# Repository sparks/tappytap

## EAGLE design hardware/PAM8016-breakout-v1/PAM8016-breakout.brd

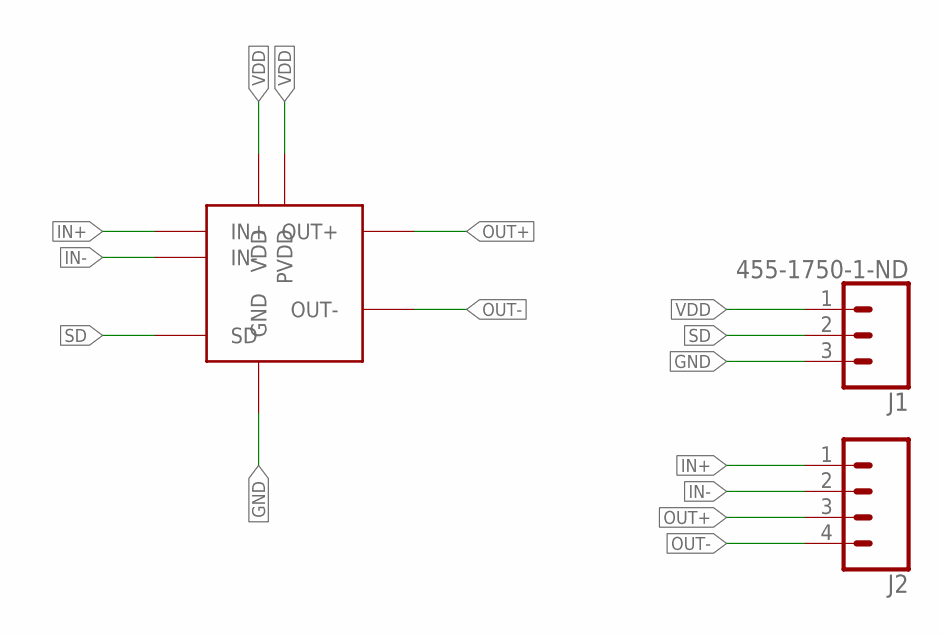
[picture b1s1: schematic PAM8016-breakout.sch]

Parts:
J1: 455-1750-1-ND; 1X03
J2: CONN_04; 1X04
U$1: PAM8016; U-FLGA1515-9

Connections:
GND: J1.3, U$1.A2 (GND), U$1.B3 (GND)
IN+: J2.1, U$1.A1 (IN+)
IN-: J2.2, U$1.C1 (IN-)
OUT+: J2.3, U$1.C3 (OUT+)
OUT-: J2.4, U$1.A3 (OUT-)
SD: J1.2, U$1.C2 (SD)
VDD: J1.1, U$1.B1 (VDD), U$1.B2 (PVDD)

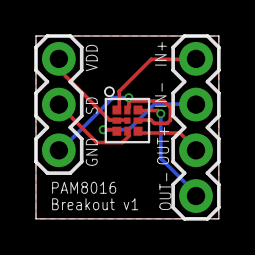
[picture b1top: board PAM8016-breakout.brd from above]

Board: 2 copper layers, 10.2 x 10.2 mm, 3 parts (0 on the bottom side), 7 nets.

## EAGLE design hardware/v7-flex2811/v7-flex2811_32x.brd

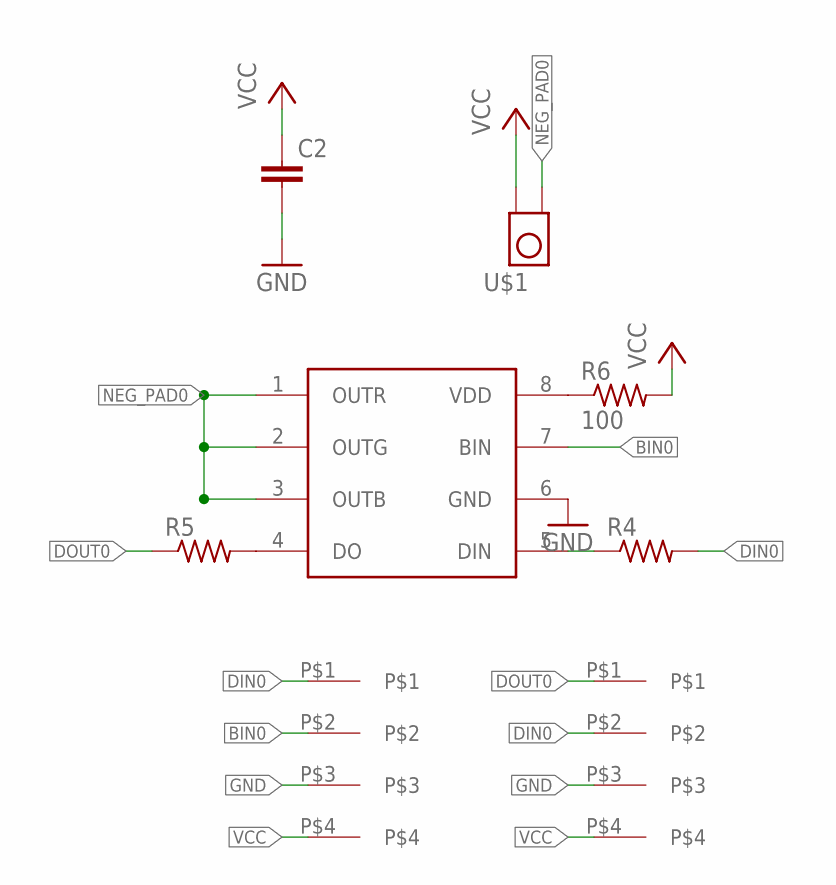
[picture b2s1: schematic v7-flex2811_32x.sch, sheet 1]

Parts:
C2: C-EUC0201; C0201
R4, R5: R-US_R0201; R0201
R6: 100; R0201
U1: WS2818; SO08
U$1: TP_4MM_MED_PAD
U$3, U$4: 4PAD

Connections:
BIN0: U1.7 (BIN), U$3.P$2
DIN0: R4.2, U$3.P$1, U$4.P$2; also elsewhere on the board
DOUT0: R5.1, U$4.P$1; also elsewhere on the board
GND: C2.2, U1.6 (GND), U$3.P$3, U$4.P$3; also elsewhere on the board
unnamed: R4.1, U1.5 (DIN)
unnamed: R5.2, U1.4 (DO)
unnamed: R6.1, U1.8 (VDD)
NEG_PAD0: U1.1 (OUTR), U1.2 (OUTG), U1.3 (OUTB), U$1.P$1 (0)
VCC: C2.1, R6.2, U$1.P$2 (1), U$3.P$4, U$4.P$4; also elsewhere on the board

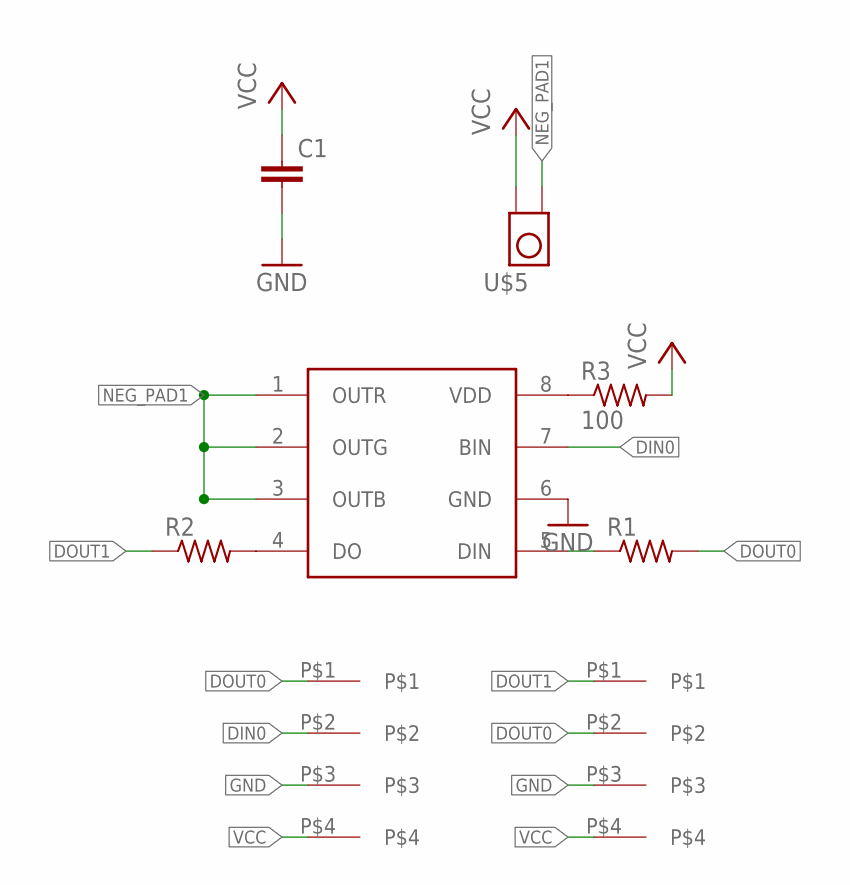
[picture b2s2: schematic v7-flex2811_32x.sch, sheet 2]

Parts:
C1: C-EUC0201; C0201
R1, R2: R-US_R0201; R0201
R3: 100; R0201
U2: WS2818; SO08
U$5: TP_4MM_MED_PAD
U$7, U$8: 4PAD

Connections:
DIN0: U2.7 (BIN), U$7.P$2; also elsewhere on the board
DOUT0: R1.2, U$7.P$1, U$8.P$2; also elsewhere on the board
DOUT1: R2.1, U$8.P$1; also elsewhere on the board
GND: C1.2, U2.6 (GND), U$7.P$3, U$8.P$3; also elsewhere on the board
unnamed: R1.1, U2.5 (DIN)
unnamed: R2.2, U2.4 (DO)
unnamed: R3.1, U2.8 (VDD)
NEG_PAD1: U2.1 (OUTR), U2.2 (OUTG), U2.3 (OUTB), U$5.P$1 (0)
VCC: C1.1, R3.2, U$5.P$2 (1), U$7.P$4, U$8.P$4; also elsewhere on the board

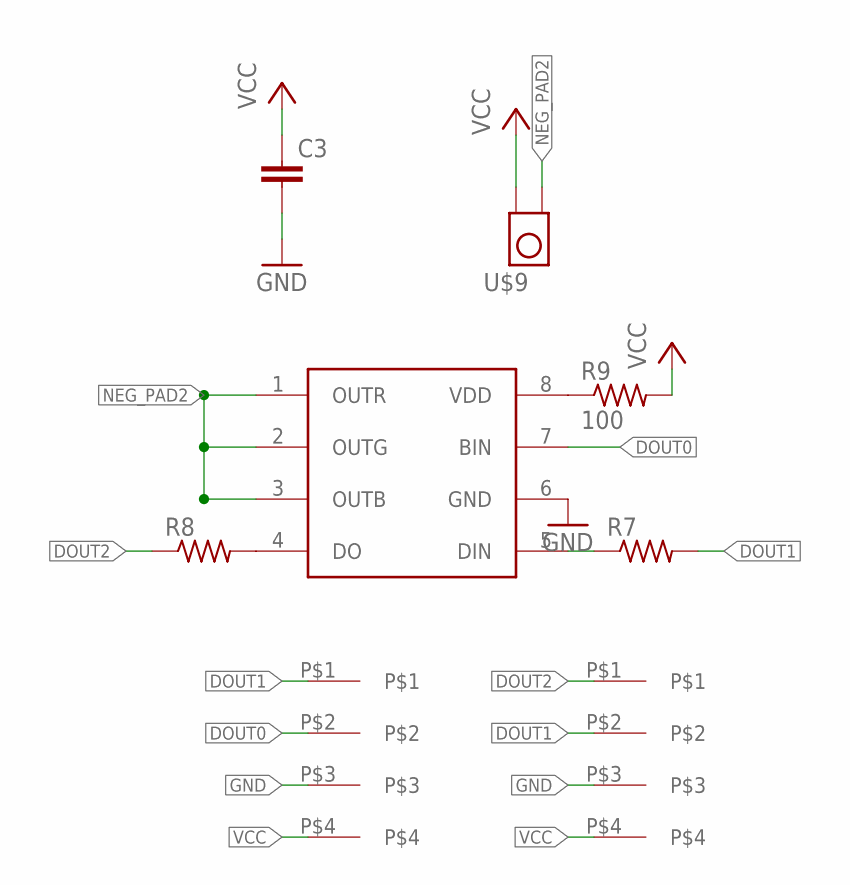
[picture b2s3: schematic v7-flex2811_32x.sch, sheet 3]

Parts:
C3: C-EUC0201; C0201
R7, R8: R-US_R0201; R0201
R9: 100; R0201
U3: WS2818; SO08
U$9: TP_4MM_MED_PAD
U$11, U$12: 4PAD

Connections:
DOUT0: U3.7 (BIN), U$11.P$2; also elsewhere on the board
DOUT1: R7.2, U$11.P$1, U$12.P$2; also elsewhere on the board
DOUT2: R8.1, U$12.P$1; also elsewhere on the board
GND: C3.2, U3.6 (GND), U$11.P$3, U$12.P$3; also elsewhere on the board
unnamed: R7.1, U3.5 (DIN)
unnamed: R8.2, U3.4 (DO)
unnamed: R9.1, U3.8 (VDD)
NEG_PAD2: U3.1 (OUTR), U3.2 (OUTG), U3.3 (OUTB), U$9.P$1 (0)
VCC: C3.1, R9.2, U$9.P$2 (1), U$11.P$4, U$12.P$4; also elsewhere on the board

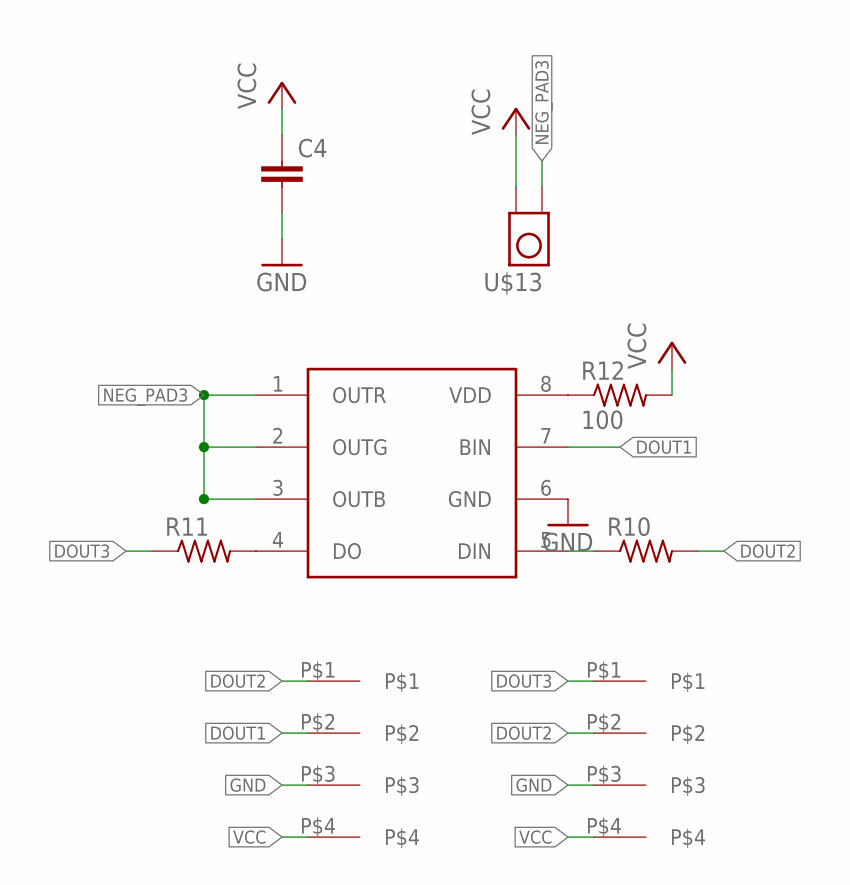
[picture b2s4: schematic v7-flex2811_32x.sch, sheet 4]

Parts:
C4: C-EUC0201; C0201
R10, R11: R-US_R0201; R0201
R12: 100; R0201
U4: WS2818; SO08
U$13: TP_4MM_MED_PAD
U$15, U$16: 4PAD

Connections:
DOUT1: U4.7 (BIN), U$15.P$2; also elsewhere on the board
DOUT2: R10.2, U$15.P$1, U$16.P$2; also elsewhere on the board
DOUT3: R11.1, U$16.P$1; also elsewhere on the board
GND: C4.2, U4.6 (GND), U$15.P$3, U$16.P$3; also elsewhere on the board
unnamed: R10.1, U4.5 (DIN)
unnamed: R11.2, U4.4 (DO)
unnamed: R12.1, U4.8 (VDD)
NEG_PAD3: U4.1 (OUTR), U4.2 (OUTG), U4.3 (OUTB), U$13.P$1 (0)
VCC: C4.1, R12.2, U$13.P$2 (1), U$15.P$4, U$16.P$4; also elsewhere on the board

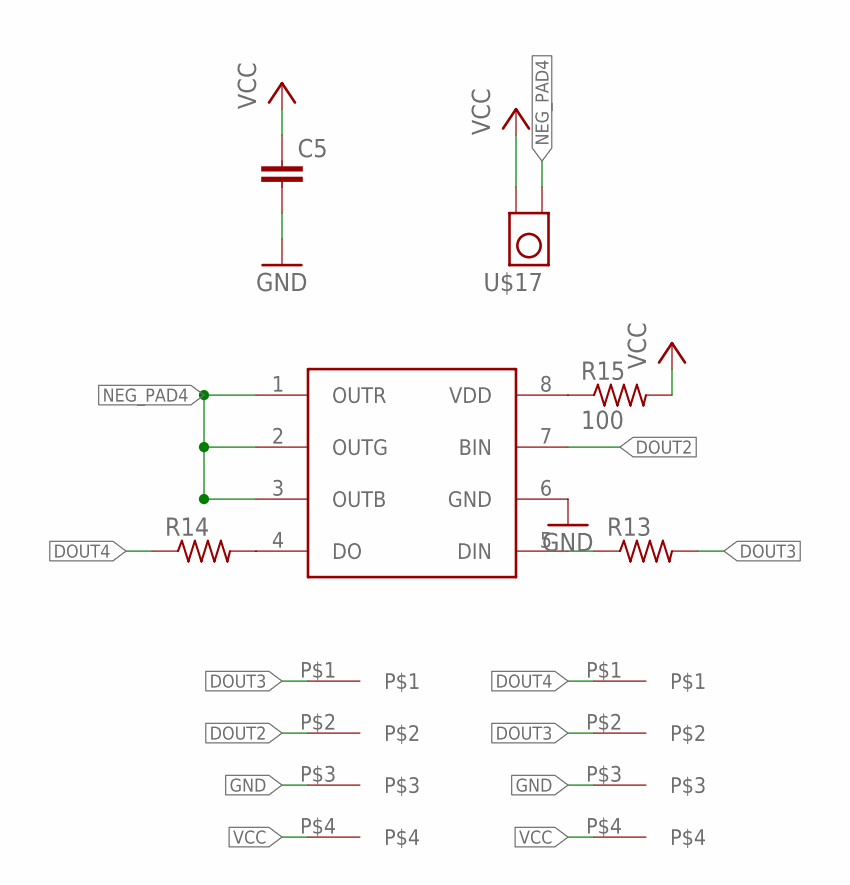
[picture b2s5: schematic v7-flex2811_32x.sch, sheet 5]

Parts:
C5: C-EUC0201; C0201
R13, R14: R-US_R0201; R0201
R15: 100; R0201
U5: WS2818; SO08
U$17: TP_4MM_MED_PAD
U$19, U$20: 4PAD

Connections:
DOUT2: U5.7 (BIN), U$19.P$2; also elsewhere on the board
DOUT3: R13.2, U$19.P$1, U$20.P$2; also elsewhere on the board
DOUT4: R14.1, U$20.P$1; also elsewhere on the board
GND: C5.2, U5.6 (GND), U$19.P$3, U$20.P$3; also elsewhere on the board
unnamed: R13.1, U5.5 (DIN)
unnamed: R14.2, U5.4 (DO)
unnamed: R15.1, U5.8 (VDD)
NEG_PAD4: U5.1 (OUTR), U5.2 (OUTG), U5.3 (OUTB), U$17.P$1 (0)
VCC: C5.1, R15.2, U$17.P$2 (1), U$19.P$4, U$20.P$4; also elsewhere on the board

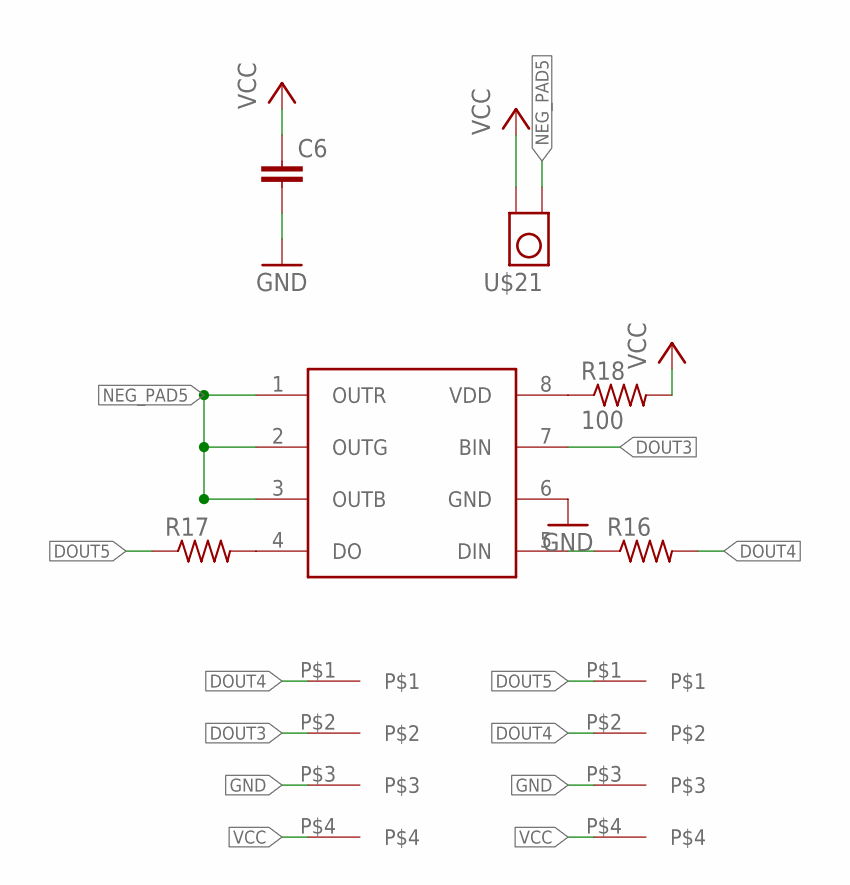
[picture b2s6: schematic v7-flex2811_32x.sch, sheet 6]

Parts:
C6: C-EUC0201; C0201
R16, R17: R-US_R0201; R0201
R18: 100; R0201
U6: WS2818; SO08
U$21: TP_4MM_MED_PAD
U$23, U$24: 4PAD

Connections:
DOUT3: U6.7 (BIN), U$23.P$2; also elsewhere on the board
DOUT4: R16.2, U$23.P$1, U$24.P$2; also elsewhere on the board
DOUT5: R17.1, U$24.P$1; also elsewhere on the board
GND: C6.2, U6.6 (GND), U$23.P$3, U$24.P$3; also elsewhere on the board
unnamed: R16.1, U6.5 (DIN)
unnamed: R17.2, U6.4 (DO)
unnamed: R18.1, U6.8 (VDD)
NEG_PAD5: U6.1 (OUTR), U6.2 (OUTG), U6.3 (OUTB), U$21.P$1 (0)
VCC: C6.1, R18.2, U$21.P$2 (1), U$23.P$4, U$24.P$4; also elsewhere on the board

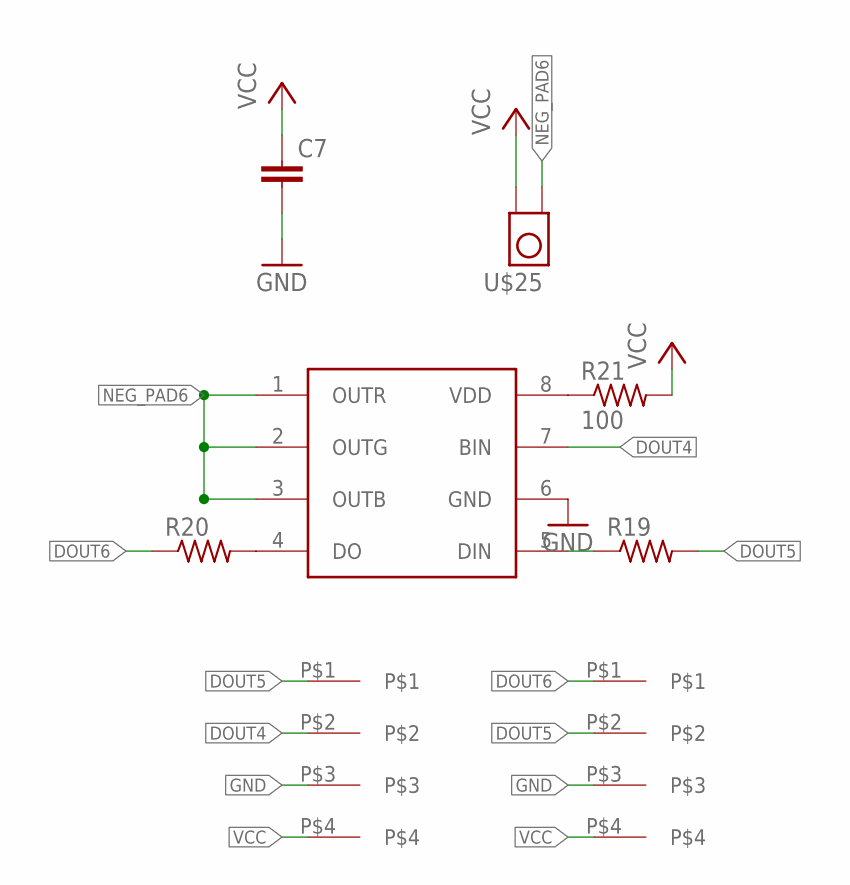
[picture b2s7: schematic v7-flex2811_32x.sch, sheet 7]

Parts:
C7: C-EUC0201; C0201
R19, R20: R-US_R0201; R0201
R21: 100; R0201
U7: WS2818; SO08
U$25: TP_4MM_MED_PAD
U$27, U$28: 4PAD

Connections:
DOUT4: U7.7 (BIN), U$27.P$2; also elsewhere on the board
DOUT5: R19.2, U$27.P$1, U$28.P$2; also elsewhere on the board
DOUT6: R20.1, U$28.P$1; also elsewhere on the board
GND: C7.2, U7.6 (GND), U$27.P$3, U$28.P$3; also elsewhere on the board
unnamed: R19.1, U7.5 (DIN)
unnamed: R20.2, U7.4 (DO)
unnamed: R21.1, U7.8 (VDD)
NEG_PAD6: U7.1 (OUTR), U7.2 (OUTG), U7.3 (OUTB), U$25.P$1 (0)
VCC: C7.1, R21.2, U$25.P$2 (1), U$27.P$4, U$28.P$4; also elsewhere on the board

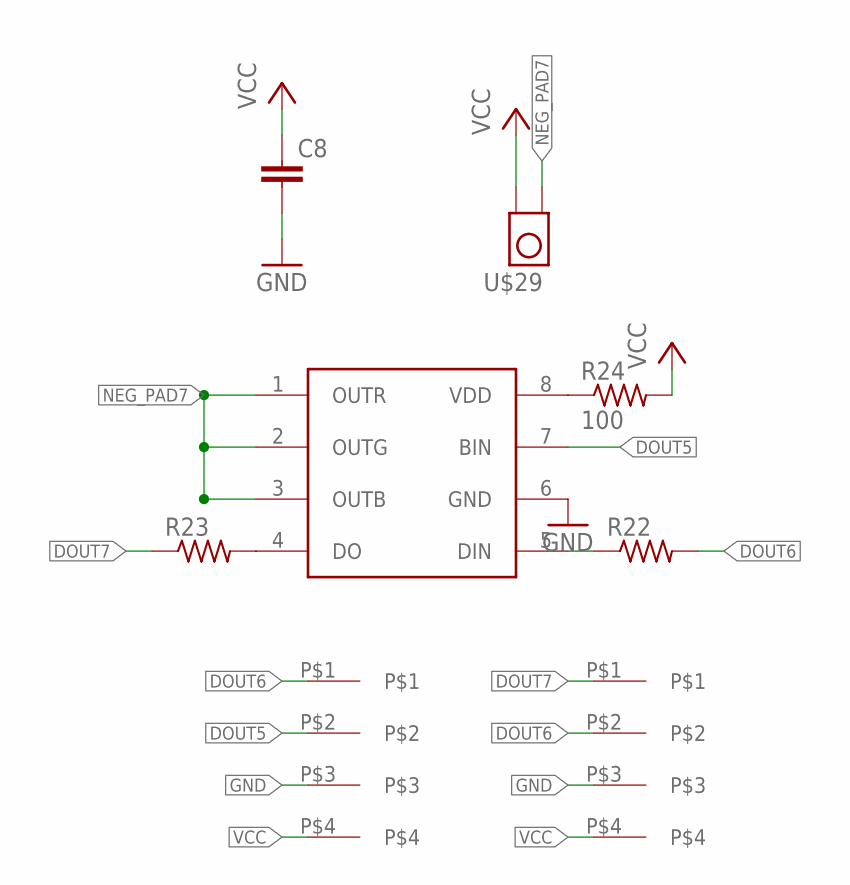
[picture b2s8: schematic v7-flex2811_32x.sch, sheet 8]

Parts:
C8: C-EUC0201; C0201
R22, R23: R-US_R0201; R0201
R24: 100; R0201
U8: WS2818; SO08
U$29: TP_4MM_MED_PAD
U$31, U$32: 4PAD

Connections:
DOUT5: U8.7 (BIN), U$31.P$2; also elsewhere on the board
DOUT6: R22.2, U$31.P$1, U$32.P$2; also elsewhere on the board
DOUT7: R23.1, U$32.P$1; also elsewhere on the board
GND: C8.2, U8.6 (GND), U$31.P$3, U$32.P$3; also elsewhere on the board
unnamed: R22.1, U8.5 (DIN)
unnamed: R23.2, U8.4 (DO)
unnamed: R24.1, U8.8 (VDD)
NEG_PAD7: U8.1 (OUTR), U8.2 (OUTG), U8.3 (OUTB), U$29.P$1 (0)
VCC: C8.1, R24.2, U$29.P$2 (1), U$31.P$4, U$32.P$4; also elsewhere on the board

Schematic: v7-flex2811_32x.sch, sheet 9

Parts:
C9: C-EUC0201; C0201
R25, R26: R-US_R0201; R0201
R27: 100; R0201
U9: WS2818; SO08
U$33: TP_4MM_MED_PAD
U$35, U$36: 4PAD

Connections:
DOUT6: U9.7 (BIN), U$35.P$2; also elsewhere on the board
DOUT7: R25.2, U$35.P$1, U$36.P$2; also elsewhere on the board
DOUT8: R26.1, U$36.P$1; also elsewhere on the board
GND: C9.2, U9.6 (GND), U$35.P$3, U$36.P$3; also elsewhere on the board
unnamed: R25.1, U9.5 (DIN)
unnamed: R26.2, U9.4 (DO)
unnamed: R27.1, U9.8 (VDD)
NEG_PAD8: U9.1 (OUTR), U9.2 (OUTG), U9.3 (OUTB), U$33.P$1 (0)
VCC: C9.1, R27.2, U$33.P$2 (1), U$35.P$4, U$36.P$4; also elsewhere on the board

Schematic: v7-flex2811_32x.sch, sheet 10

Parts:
C10: C-EUC0201; C0201
R28, R29: R-US_R0201; R0201
R30: 100; R0201
U10: WS2818; SO08
U$37: TP_4MM_MED_PAD
U$39, U$40: 4PAD

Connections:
DOUT7: U10.7 (BIN), U$39.P$2; also elsewhere on the board
DOUT8: R28.2, U$39.P$1, U$40.P$2; also elsewhere on the board
DOUT9: R29.1, U$40.P$1; also elsewhere on the board
GND: C10.2, U10.6 (GND), U$39.P$3, U$40.P$3; also elsewhere on the board
unnamed: R28.1, U10.5 (DIN)
unnamed: R29.2, U10.4 (DO)
unnamed: R30.1, U10.8 (VDD)
NEG_PAD9: U10.1 (OUTR), U10.2 (OUTG), U10.3 (OUTB), U$37.P$1 (0)
VCC: C10.1, R30.2, U$37.P$2 (1), U$39.P$4, U$40.P$4; also elsewhere on the board

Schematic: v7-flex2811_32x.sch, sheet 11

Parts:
C11: C-EUC0201; C0201
R31, R32: R-US_R0201; R0201
R33: 100; R0201
U11: WS2818; SO08
U$41: TP_4MM_MED_PAD
U$43, U$44: 4PAD

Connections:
DOUT8: U11.7 (BIN), U$43.P$2; also elsewhere on the board
DOUT9: R31.2, U$43.P$1, U$44.P$2; also elsewhere on the board
DOUT10: R32.1, U$44.P$1; also elsewhere on the board
GND: C11.2, U11.6 (GND), U$43.P$3, U$44.P$3; also elsewhere on the board
unnamed: R31.1, U11.5 (DIN)
unnamed: R32.2, U11.4 (DO)
unnamed: R33.1, U11.8 (VDD)
NEG_PAD10: U11.1 (OUTR), U11.2 (OUTG), U11.3 (OUTB), U$41.P$1 (0)
VCC: C11.1, R33.2, U$41.P$2 (1), U$43.P$4, U$44.P$4; also elsewhere on the board

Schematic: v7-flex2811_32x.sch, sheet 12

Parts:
C12: C-EUC0201; C0201
R34, R35: R-US_R0201; R0201
R36: 100; R0201
U12: WS2818; SO08
U$45: TP_4MM_MED_PAD
U$47, U$48: 4PAD

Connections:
DOUT9: U12.7 (BIN), U$47.P$2; also elsewhere on the board
DOUT10: R34.2, U$47.P$1, U$48.P$2; also elsewhere on the board
DOUT11: R35.1, U$48.P$1; also elsewhere on the board
GND: C12.2, U12.6 (GND), U$47.P$3, U$48.P$3; also elsewhere on the board
unnamed: R34.1, U12.5 (DIN)
unnamed: R35.2, U12.4 (DO)
unnamed: R36.1, U12.8 (VDD)
NEG_PAD11: U12.1 (OUTR), U12.2 (OUTG), U12.3 (OUTB), U$45.P$1 (0)
VCC: C12.1, R36.2, U$45.P$2 (1), U$47.P$4, U$48.P$4; also elsewhere on the board

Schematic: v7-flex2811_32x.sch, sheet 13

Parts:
C13: C-EUC0201; C0201
R37, R38: R-US_R0201; R0201
R39: 100; R0201
U13: WS2818; SO08
U$49: TP_4MM_MED_PAD
U$51, U$52: 4PAD

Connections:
DOUT10: U13.7 (BIN), U$51.P$2; also elsewhere on the board
DOUT11: R37.2, U$51.P$1, U$52.P$2; also elsewhere on the board
DOUT12: R38.1, U$52.P$1; also elsewhere on the board
GND: C13.2, U13.6 (GND), U$51.P$3, U$52.P$3; also elsewhere on the board
unnamed: R37.1, U13.5 (DIN)
unnamed: R38.2, U13.4 (DO)
unnamed: R39.1, U13.8 (VDD)
NEG_PAD12: U13.1 (OUTR), U13.2 (OUTG), U13.3 (OUTB), U$49.P$1 (0)
VCC: C13.1, R39.2, U$49.P$2 (1), U$51.P$4, U$52.P$4; also elsewhere on the board

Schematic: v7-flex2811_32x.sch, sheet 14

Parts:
C14: C-EUC0201; C0201
R40, R41: R-US_R0201; R0201
R42: 100; R0201
U14: WS2818; SO08
U$53: TP_4MM_MED_PAD
U$55, U$56: 4PAD

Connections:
DOUT11: U14.7 (BIN), U$55.P$2; also elsewhere on the board
DOUT12: R40.2, U$55.P$1, U$56.P$2; also elsewhere on the board
DOUT13: R41.1, U$56.P$1; also elsewhere on the board
GND: C14.2, U14.6 (GND), U$55.P$3, U$56.P$3; also elsewhere on the board
unnamed: R40.1, U14.5 (DIN)
unnamed: R41.2, U14.4 (DO)
unnamed: R42.1, U14.8 (VDD)
NEG_PAD13: U14.1 (OUTR), U14.2 (OUTG), U14.3 (OUTB), U$53.P$1 (0)
VCC: C14.1, R42.2, U$53.P$2 (1), U$55.P$4, U$56.P$4; also elsewhere on the board

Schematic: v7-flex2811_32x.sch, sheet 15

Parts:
C15: C-EUC0201; C0201
R43, R44: R-US_R0201; R0201
R45: 100; R0201
U15: WS2818; SO08
U$57: TP_4MM_MED_PAD
U$59, U$60: 4PAD

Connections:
DOUT12: U15.7 (BIN), U$59.P$2; also elsewhere on the board
DOUT13: R43.2, U$59.P$1, U$60.P$2; also elsewhere on the board
DOUT14: R44.1, U$60.P$1; also elsewhere on the board
GND: C15.2, U15.6 (GND), U$59.P$3, U$60.P$3; also elsewhere on the board
unnamed: R43.1, U15.5 (DIN)
unnamed: R44.2, U15.4 (DO)
unnamed: R45.1, U15.8 (VDD)
NEG_PAD14: U15.1 (OUTR), U15.2 (OUTG), U15.3 (OUTB), U$57.P$1 (0)
VCC: C15.1, R45.2, U$57.P$2 (1), U$59.P$4, U$60.P$4; also elsewhere on the board

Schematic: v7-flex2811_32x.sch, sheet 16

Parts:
C16: C-EUC0201; C0201
R46, R47: R-US_R0201; R0201
R48: 100; R0201
U16: WS2818; SO08
U$61: TP_4MM_MED_PAD
U$63, U$64: 4PAD

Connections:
DOUT13: U16.7 (BIN), U$63.P$2; also elsewhere on the board
DOUT14: R46.2, U$63.P$1, U$64.P$2; also elsewhere on the board
DOUT15: R47.1, U$64.P$1; also elsewhere on the board
GND: C16.2, U16.6 (GND), U$63.P$3, U$64.P$3; also elsewhere on the board
unnamed: R46.1, U16.5 (DIN)
unnamed: R47.2, U16.4 (DO)
unnamed: R48.1, U16.8 (VDD)
NEG_PAD15: U16.1 (OUTR), U16.2 (OUTG), U16.3 (OUTB), U$61.P$1 (0)
VCC: C16.1, R48.2, U$61.P$2 (1), U$63.P$4, U$64.P$4; also elsewhere on the board

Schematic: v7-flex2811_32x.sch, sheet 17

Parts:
C17: C-EUC0201; C0201
R49, R50: R-US_R0201; R0201
R51: 100; R0201
U17: WS2818; SO08
U$65: TP_4MM_MED_PAD
U$67, U$68: 4PAD

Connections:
DOUT14: U17.7 (BIN), U$67.P$2; also elsewhere on the board
DOUT15: R49.2, U$67.P$1, U$68.P$2; also elsewhere on the board
DOUT16: R50.1, U$68.P$1; also elsewhere on the board
GND: C17.2, U17.6 (GND), U$67.P$3, U$68.P$3; also elsewhere on the board
unnamed: R49.1, U17.5 (DIN)
unnamed: R50.2, U17.4 (DO)
unnamed: R51.1, U17.8 (VDD)
NEG_PAD16: U17.1 (OUTR), U17.2 (OUTG), U17.3 (OUTB), U$65.P$1 (0)
VCC: C17.1, R51.2, U$65.P$2 (1), U$67.P$4, U$68.P$4; also elsewhere on the board

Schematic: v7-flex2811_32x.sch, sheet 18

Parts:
C18: C-EUC0201; C0201
R52, R53: R-US_R0201; R0201
R54: 100; R0201
U18: WS2818; SO08
U$69: TP_4MM_MED_PAD
U$71, U$72: 4PAD

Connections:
DOUT15: U18.7 (BIN), U$71.P$2; also elsewhere on the board
DOUT16: R52.2, U$71.P$1, U$72.P$2; also elsewhere on the board
DOUT17: R53.1, U$72.P$1; also elsewhere on the board
GND: C18.2, U18.6 (GND), U$71.P$3, U$72.P$3; also elsewhere on the board
unnamed: R52.1, U18.5 (DIN)
unnamed: R53.2, U18.4 (DO)
unnamed: R54.1, U18.8 (VDD)
NEG_PAD17: U18.1 (OUTR), U18.2 (OUTG), U18.3 (OUTB), U$69.P$1 (0)
VCC: C18.1, R54.2, U$69.P$2 (1), U$71.P$4, U$72.P$4; also elsewhere on the board

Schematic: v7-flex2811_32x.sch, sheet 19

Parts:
C19: C-EUC0201; C0201
R55, R56: R-US_R0201; R0201
R57: 100; R0201
U19: WS2818; SO08
U$73: TP_4MM_MED_PAD
U$75, U$76: 4PAD

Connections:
DOUT16: U19.7 (BIN), U$75.P$2; also elsewhere on the board
DOUT17: R55.2, U$75.P$1, U$76.P$2; also elsewhere on the board
DOUT18: R56.1, U$76.P$1; also elsewhere on the board
GND: C19.2, U19.6 (GND), U$75.P$3, U$76.P$3; also elsewhere on the board
unnamed: R55.1, U19.5 (DIN)
unnamed: R56.2, U19.4 (DO)
unnamed: R57.1, U19.8 (VDD)
NEG_PAD18: U19.1 (OUTR), U19.2 (OUTG), U19.3 (OUTB), U$73.P$1 (0)
VCC: C19.1, R57.2, U$73.P$2 (1), U$75.P$4, U$76.P$4; also elsewhere on the board

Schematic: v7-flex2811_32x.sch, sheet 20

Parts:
C20: C-EUC0201; C0201
R58, R59: R-US_R0201; R0201
R60: 100; R0201
U20: WS2818; SO08
U$77: TP_4MM_MED_PAD
U$79, U$80: 4PAD

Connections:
DOUT17: U20.7 (BIN), U$79.P$2; also elsewhere on the board
DOUT18: R58.2, U$79.P$1, U$80.P$2; also elsewhere on the board
DOUT19: R59.1, U$80.P$1; also elsewhere on the board
GND: C20.2, U20.6 (GND), U$79.P$3, U$80.P$3; also elsewhere on the board
unnamed: R58.1, U20.5 (DIN)
unnamed: R59.2, U20.4 (DO)
unnamed: R60.1, U20.8 (VDD)
NEG_PAD19: U20.1 (OUTR), U20.2 (OUTG), U20.3 (OUTB), U$77.P$1 (0)
VCC: C20.1, R60.2, U$77.P$2 (1), U$79.P$4, U$80.P$4; also elsewhere on the board

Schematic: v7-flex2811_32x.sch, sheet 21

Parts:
C21: C-EUC0201; C0201
R61, R62: R-US_R0201; R0201
R63: 100; R0201
U21: WS2818; SO08
U$81: TP_4MM_MED_PAD
U$83, U$84: 4PAD

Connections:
DOUT18: U21.7 (BIN), U$83.P$2; also elsewhere on the board
DOUT19: R61.2, U$83.P$1, U$84.P$2; also elsewhere on the board
DOUT20: R62.1, U$84.P$1; also elsewhere on the board
GND: C21.2, U21.6 (GND), U$83.P$3, U$84.P$3; also elsewhere on the board
unnamed: R61.1, U21.5 (DIN)
unnamed: R62.2, U21.4 (DO)
unnamed: R63.1, U21.8 (VDD)
NEG_PAD20: U21.1 (OUTR), U21.2 (OUTG), U21.3 (OUTB), U$81.P$1 (0)
VCC: C21.1, R63.2, U$81.P$2 (1), U$83.P$4, U$84.P$4; also elsewhere on the board

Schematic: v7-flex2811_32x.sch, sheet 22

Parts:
C22: C-EUC0201; C0201
R64, R65: R-US_R0201; R0201
R66: 100; R0201
U22: WS2818; SO08
U$85: TP_4MM_MED_PAD
U$87, U$88: 4PAD

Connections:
DOUT19: U22.7 (BIN), U$87.P$2; also elsewhere on the board
DOUT20: R64.2, U$87.P$1, U$88.P$2; also elsewhere on the board
DOUT21: R65.1, U$88.P$1; also elsewhere on the board
GND: C22.2, U22.6 (GND), U$87.P$3, U$88.P$3; also elsewhere on the board
unnamed: R64.1, U22.5 (DIN)
unnamed: R65.2, U22.4 (DO)
unnamed: R66.1, U22.8 (VDD)
NEG_PAD21: U22.1 (OUTR), U22.2 (OUTG), U22.3 (OUTB), U$85.P$1 (0)
VCC: C22.1, R66.2, U$85.P$2 (1), U$87.P$4, U$88.P$4; also elsewhere on the board

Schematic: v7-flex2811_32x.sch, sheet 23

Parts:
C23: C-EUC0201; C0201
R67, R68: R-US_R0201; R0201
R69: 100; R0201
U23: WS2818; SO08
U$89: TP_4MM_MED_PAD
U$91, U$92: 4PAD

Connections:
DOUT20: U23.7 (BIN), U$91.P$2; also elsewhere on the board
DOUT21: R67.2, U$91.P$1, U$92.P$2; also elsewhere on the board
DOUT22: R68.1, U$92.P$1; also elsewhere on the board
GND: C23.2, U23.6 (GND), U$91.P$3, U$92.P$3; also elsewhere on the board
unnamed: R67.1, U23.5 (DIN)
unnamed: R68.2, U23.4 (DO)
unnamed: R69.1, U23.8 (VDD)
NEG_PAD22: U23.1 (OUTR), U23.2 (OUTG), U23.3 (OUTB), U$89.P$1 (0)
VCC: C23.1, R69.2, U$89.P$2 (1), U$91.P$4, U$92.P$4; also elsewhere on the board

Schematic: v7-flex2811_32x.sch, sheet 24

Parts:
C24: C-EUC0201; C0201
R70, R71: R-US_R0201; R0201
R72: 100; R0201
U24: WS2818; SO08
U$93: TP_4MM_MED_PAD
U$95, U$96: 4PAD

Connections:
DOUT21: U24.7 (BIN), U$95.P$2; also elsewhere on the board
DOUT22: R70.2, U$95.P$1, U$96.P$2; also elsewhere on the board
DOUT23: R71.1, U$96.P$1; also elsewhere on the board
GND: C24.2, U24.6 (GND), U$95.P$3, U$96.P$3; also elsewhere on the board
unnamed: R70.1, U24.5 (DIN)
unnamed: R71.2, U24.4 (DO)
unnamed: R72.1, U24.8 (VDD)
NEG_PAD23: U24.1 (OUTR), U24.2 (OUTG), U24.3 (OUTB), U$93.P$1 (0)
VCC: C24.1, R72.2, U$93.P$2 (1), U$95.P$4, U$96.P$4; also elsewhere on the board

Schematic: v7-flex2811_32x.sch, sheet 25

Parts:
C25: C-EUC0201; C0201
R73, R74: R-US_R0201; R0201
R75: 100; R0201
U25: WS2818; SO08
U$97: TP_4MM_MED_PAD
U$99, U$100: 4PAD

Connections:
DOUT22: U25.7 (BIN), U$99.P$2; also elsewhere on the board
DOUT23: R73.2, U$99.P$1, U$100.P$2; also elsewhere on the board
DOUT24: R74.1, U$100.P$1; also elsewhere on the board
GND: C25.2, U25.6 (GND), U$99.P$3, U$100.P$3; also elsewhere on the board
unnamed: R73.1, U25.5 (DIN)
unnamed: R74.2, U25.4 (DO)
unnamed: R75.1, U25.8 (VDD)
NEG_PAD24: U25.1 (OUTR), U25.2 (OUTG), U25.3 (OUTB), U$97.P$1 (0)
VCC: C25.1, R75.2, U$97.P$2 (1), U$99.P$4, U$100.P$4; also elsewhere on the board

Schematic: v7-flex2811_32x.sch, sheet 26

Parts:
C26: C-EUC0201; C0201
R76, R77: R-US_R0201; R0201
R78: 100; R0201
U26: WS2818; SO08
U$101: TP_4MM_MED_PAD
U$103, U$104: 4PAD

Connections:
DOUT23: U26.7 (BIN), U$103.P$2; also elsewhere on the board
DOUT24: R76.2, U$103.P$1, U$104.P$2; also elsewhere on the board
DOUT25: R77.1, U$104.P$1; also elsewhere on the board
GND: C26.2, U26.6 (GND), U$103.P$3, U$104.P$3; also elsewhere on the board
unnamed: R76.1, U26.5 (DIN)
unnamed: R77.2, U26.4 (DO)
unnamed: R78.1, U26.8 (VDD)
NEG_PAD25: U26.1 (OUTR), U26.2 (OUTG), U26.3 (OUTB), U$101.P$1 (0)
VCC: C26.1, R78.2, U$101.P$2 (1), U$103.P$4, U$104.P$4; also elsewhere on the board

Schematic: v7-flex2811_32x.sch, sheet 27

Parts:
C27: C-EUC0201; C0201
R79, R80: R-US_R0201; R0201
R81: 100; R0201
U27: WS2818; SO08
U$105: TP_4MM_MED_PAD
U$107, U$108: 4PAD

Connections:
DOUT24: U27.7 (BIN), U$107.P$2; also elsewhere on the board
DOUT25: R79.2, U$107.P$1, U$108.P$2; also elsewhere on the board
DOUT26: R80.1, U$108.P$1; also elsewhere on the board
GND: C27.2, U27.6 (GND), U$107.P$3, U$108.P$3; also elsewhere on the board
unnamed: R79.1, U27.5 (DIN)
unnamed: R80.2, U27.4 (DO)
unnamed: R81.1, U27.8 (VDD)
NEG_PAD26: U27.1 (OUTR), U27.2 (OUTG), U27.3 (OUTB), U$105.P$1 (0)
VCC: C27.1, R81.2, U$105.P$2 (1), U$107.P$4, U$108.P$4; also elsewhere on the board

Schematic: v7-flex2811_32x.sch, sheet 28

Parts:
C28: C-EUC0201; C0201
R82, R83: R-US_R0201; R0201
R84: 100; R0201
U28: WS2818; SO08
U$109: TP_4MM_MED_PAD
U$111, U$112: 4PAD

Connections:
DOUT25: U28.7 (BIN), U$111.P$2; also elsewhere on the board
DOUT26: R82.2, U$111.P$1, U$112.P$2; also elsewhere on the board
DOUT27: R83.1, U$112.P$1; also elsewhere on the board
GND: C28.2, U28.6 (GND), U$111.P$3, U$112.P$3; also elsewhere on the board
unnamed: R82.1, U28.5 (DIN)
unnamed: R83.2, U28.4 (DO)
unnamed: R84.1, U28.8 (VDD)
NEG_PAD27: U28.1 (OUTR), U28.2 (OUTG), U28.3 (OUTB), U$109.P$1 (0)
VCC: C28.1, R84.2, U$109.P$2 (1), U$111.P$4, U$112.P$4; also elsewhere on the board

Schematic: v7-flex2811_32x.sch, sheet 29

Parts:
C29: C-EUC0201; C0201
R85, R86: R-US_R0201; R0201
R87: 100; R0201
U29: WS2818; SO08
U$113: TP_4MM_MED_PAD
U$115, U$116: 4PAD

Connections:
DOUT26: U29.7 (BIN), U$115.P$2; also elsewhere on the board
DOUT27: R85.2, U$115.P$1, U$116.P$2; also elsewhere on the board
DOUT28: R86.1, U$116.P$1; also elsewhere on the board
GND: C29.2, U29.6 (GND), U$115.P$3, U$116.P$3; also elsewhere on the board
unnamed: R85.1, U29.5 (DIN)
unnamed: R86.2, U29.4 (DO)
unnamed: R87.1, U29.8 (VDD)
NEG_PAD28: U29.1 (OUTR), U29.2 (OUTG), U29.3 (OUTB), U$113.P$1 (0)
VCC: C29.1, R87.2, U$113.P$2 (1), U$115.P$4, U$116.P$4; also elsewhere on the board

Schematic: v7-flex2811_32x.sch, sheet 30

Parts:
C30: C-EUC0201; C0201
R88, R89: R-US_R0201; R0201
R90: 100; R0201
U30: WS2818; SO08
U$117: TP_4MM_MED_PAD
U$119, U$120: 4PAD

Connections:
DOUT27: U30.7 (BIN), U$119.P$2; also elsewhere on the board
DOUT28: R88.2, U$119.P$1, U$120.P$2; also elsewhere on the board
DOUT29: R89.1, U$120.P$1; also elsewhere on the board
GND: C30.2, U30.6 (GND), U$119.P$3, U$120.P$3; also elsewhere on the board
unnamed: R88.1, U30.5 (DIN)
unnamed: R89.2, U30.4 (DO)
unnamed: R90.1, U30.8 (VDD)
NEG_PAD29: U30.1 (OUTR), U30.2 (OUTG), U30.3 (OUTB), U$117.P$1 (0)
VCC: C30.1, R90.2, U$117.P$2 (1), U$119.P$4, U$120.P$4; also elsewhere on the board

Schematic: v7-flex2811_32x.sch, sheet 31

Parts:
C31: C-EUC0201; C0201
R91, R92: R-US_R0201; R0201
R93: 100; R0201
U31: WS2818; SO08
U$121: TP_4MM_MED_PAD
U$123, U$124: 4PAD

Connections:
DOUT28: U31.7 (BIN), U$123.P$2; also elsewhere on the board
DOUT29: R91.2, U$123.P$1, U$124.P$2; also elsewhere on the board
DOUT30: R92.1, U$124.P$1; also elsewhere on the board
GND: C31.2, U31.6 (GND), U$123.P$3, U$124.P$3; also elsewhere on the board
unnamed: R91.1, U31.5 (DIN)
unnamed: R92.2, U31.4 (DO)
unnamed: R93.1, U31.8 (VDD)
NEG_PAD30: U31.1 (OUTR), U31.2 (OUTG), U31.3 (OUTB), U$121.P$1 (0)
VCC: C31.1, R93.2, U$121.P$2 (1), U$123.P$4, U$124.P$4; also elsewhere on the board

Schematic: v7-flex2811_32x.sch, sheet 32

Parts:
C32: C-EUC0201; C0201
R94, R95: R-US_R0201; R0201
R96: 100; R0201
U32: WS2818; SO08
U$125: TP_4MM_MED_PAD
U$127, U$128: 4PAD

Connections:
DOUT29: U32.7 (BIN), U$127.P$2; also elsewhere on the board
DOUT30: R94.2, U$127.P$1, U$128.P$2; also elsewhere on the board
DOUT31: R95.1, U$128.P$1
GND: C32.2, U32.6 (GND), U$127.P$3, U$128.P$3; also elsewhere on the board
unnamed: R94.1, U32.5 (DIN)
unnamed: R95.2, U32.4 (DO)
unnamed: R96.1, U32.8 (VDD)
NEG_PAD31: U32.1 (OUTR), U32.2 (OUTG), U32.3 (OUTB), U$125.P$1 (0)
VCC: C32.1, R96.2, U$125.P$2 (1), U$127.P$4, U$128.P$4; also elsewhere on the board

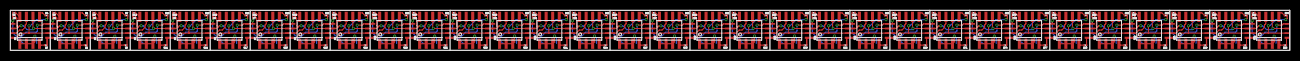
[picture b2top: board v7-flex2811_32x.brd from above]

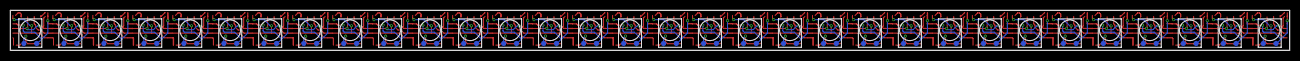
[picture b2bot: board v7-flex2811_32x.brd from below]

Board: 2 copper layers, 248.0 x 7.8 mm, 256 parts (32 on the bottom side), 164 nets.

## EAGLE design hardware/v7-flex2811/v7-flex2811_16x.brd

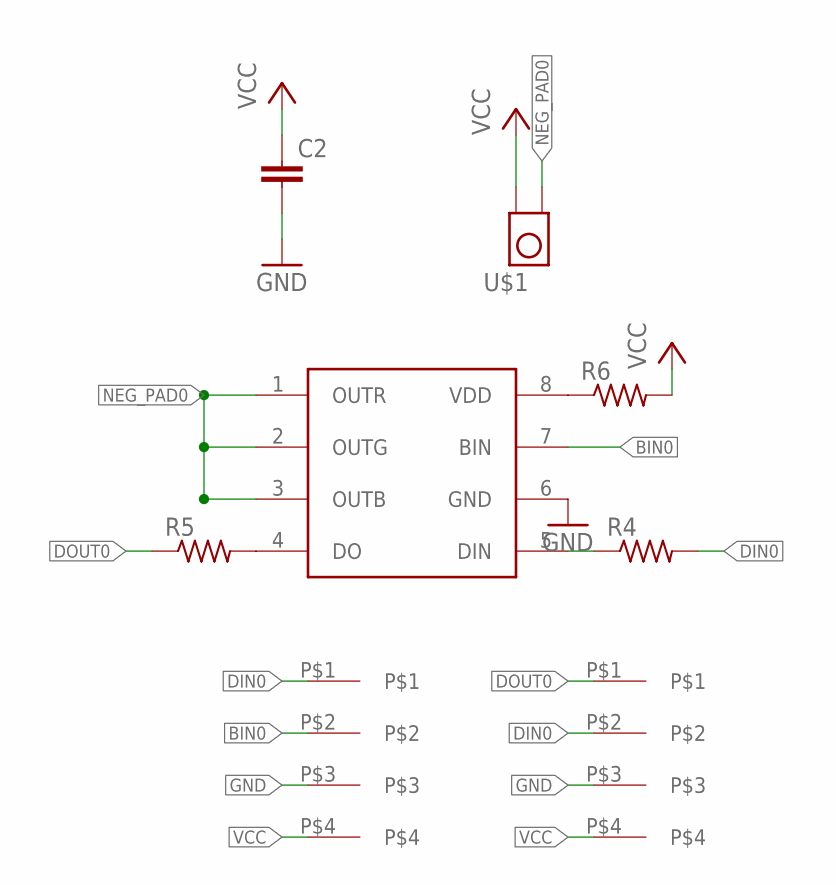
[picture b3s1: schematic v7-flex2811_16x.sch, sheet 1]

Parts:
C2: C-EUC0201; C0201
R4, R5, R6: R-US_R0201; R0201
U$1: TP_4MM_MED_PAD
U$2: WS2818; SO08
U$3, U$4: 4PAD

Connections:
BIN0: U$2.7 (BIN), U$3.P$2
DIN0: R4.2, U$3.P$1, U$4.P$2; also elsewhere on the board
DOUT0: R5.1, U$4.P$1; also elsewhere on the board
GND: C2.2, U$2.6 (GND), U$3.P$3, U$4.P$3; also elsewhere on the board
unnamed: R4.1, U$2.5 (DIN)
unnamed: R5.2, U$2.4 (DO)
unnamed: R6.1, U$2.8 (VDD)
NEG_PAD0: U$1.P$1 (0), U$2.1 (OUTR), U$2.2 (OUTG), U$2.3 (OUTB)
VCC: C2.1, R6.2, U$1.P$2 (1), U$3.P$4, U$4.P$4; also elsewhere on the board

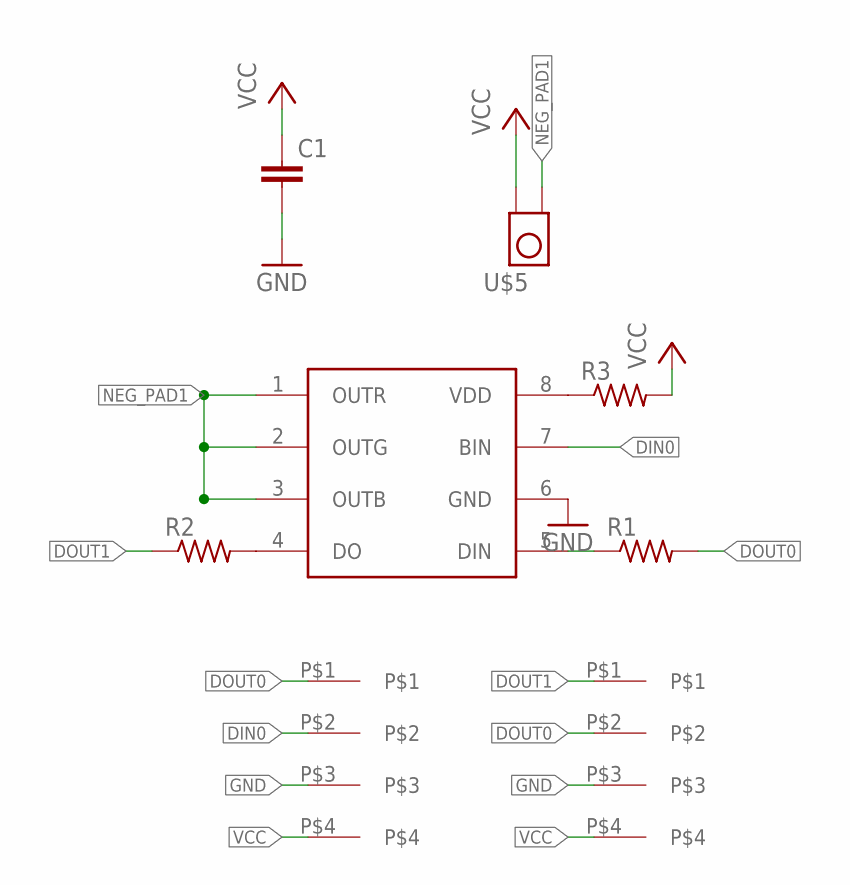
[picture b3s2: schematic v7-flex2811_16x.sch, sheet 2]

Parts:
C1: C-EUC0201; C0201
R1, R2, R3: R-US_R0201; R0201
U$5: TP_4MM_MED_PAD
U$6: WS2818; SO08
U$7, U$8: 4PAD

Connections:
DIN0: U$6.7 (BIN), U$7.P$2; also elsewhere on the board
DOUT0: R1.2, U$7.P$1, U$8.P$2; also elsewhere on the board
DOUT1: R2.1, U$8.P$1; also elsewhere on the board
GND: C1.2, U$6.6 (GND), U$7.P$3, U$8.P$3; also elsewhere on the board
unnamed: R1.1, U$6.5 (DIN)
unnamed: R2.2, U$6.4 (DO)
unnamed: R3.1, U$6.8 (VDD)
NEG_PAD1: U$5.P$1 (0), U$6.1 (OUTR), U$6.2 (OUTG), U$6.3 (OUTB)
VCC: C1.1, R3.2, U$5.P$2 (1), U$7.P$4, U$8.P$4; also elsewhere on the board

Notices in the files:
parts and their libraries:
SparkFun-Connectors: Licensing: Creative Commons ShareAlike 4.0 International - https://creativecommons.org/licenses/by-sa/4.0
